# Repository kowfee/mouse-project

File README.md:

# mouse-diy
this project was inspired by https://github.com/wareya/DIY-Gaming-Mouse

!!!! ----- DO NOT CHANGE THE STRUCTURE OF THE FILES AND DIRECTORIES IN 'mouse-diy' ---- !!!!

!!!! ----- src/srom_3360_0x04.h should contain copyrighted material, so it is not included in this repository. 0x00 should be replaced with a correct sequence, available on the internet ---- !!!!
!!!! ----- it is firmware for the pmw3360 sensor. it will function without the firmware, however loses some of the functionality and precision ---- !!!!

[INSTALLATION]

- Windows: 
    - within the 'dist' folder run the "installer.exe"

- Linux: 
    - run the following commands from the 'mouse-diy' directory in the terminal:
        - chmod 744 bin/arduino-cli
        - chmod 744 dist/interface
        - bin/arduino-cli core install arduino:mbed_rp2040@4.1.5
        - sudo $HOME/.arduino15/packages/arduino/hardware/mbed_rp2040/4.1.5/post_install.sh
        - bin/arduino-cli config set library.enable_unsafe_install true
        - bin/arduino-cli lib install --zip-path files/Adafruit_NeoPixel-1.12.3.zip

[HOW TO USE]

- Windows:
    - run the 'interface.exe' within the 'dist' folder

- Linux:
    - from the 'mouse-diy' directory run the following command:
        - dist/interface

The user interface lets you choose how many DPI settings you want to save and the DPI for each setting. You can also adjust the RGB color for the static setting.

[UNINSTALL]

- Windows: 
    - run the following commands in CMD:
        - rmdir /s /q %USERPROFILE%\AppData\Local\Arduino15\packages\arduino\hardware\mbed_rp2040\
        - rmdir /s /q %USERPROFILE%\Documents\Arduino\libraries\Adafruit_NeoPixel\

- Linux:
    - run the following commands in the terminal:
        - rm -rf $HOME/.arduino15/packages/arduino/hardware/mbed_rp2040/
        - rm -rf $HOME/Arduino/libraries/Adafruit_Neopixel/

[LICENSE]
Adafruit NeoPixel is licensed under GNU Lesser General Public License https://github.com/adafruit/Adafruit_NeoPixel

Arduino CLI is licensed under GNU General Public License https://github.com/arduino/arduino-cli

relmouse_16.h is based on files from mbed OS, also licensed under the Apache License, version 2.0. https://github.com/arduino/ArduinoCore-mbed

The hardware design files ("PCB mit LED", "PCB_Fabrication_Files" "Fusion360-Base.f3z" and "Fusion360-Body.f3z") are licensed under the SolderpadLicense, version 2.1, as follows:
```
Copyright 2024 Pasty6969, klibandm, kowfee
SPDX-License-Identifier: Apache-2.0 WITH SHL-2.1

Licensed under the Solderpad Hardware License v 2.1 (the “License”); you may not use this file except in compliance with the License, or, at your option, the Apache License version 2.0. You may obtain a copy of the License at

https://solderpad.org/licenses/SHL-2.1/

Unless required by applicable law or agreed to in writing, any work distributed under the License is distributed on an “AS IS” BASIS, WITHOUT WARRANTIES OR CONDITIONS OF ANY KIND, either express or implied. See the License for the specific language governing permissions and limitations under the License.
```

mouse-diy.ino as well as other file contents are licensed under MIT License

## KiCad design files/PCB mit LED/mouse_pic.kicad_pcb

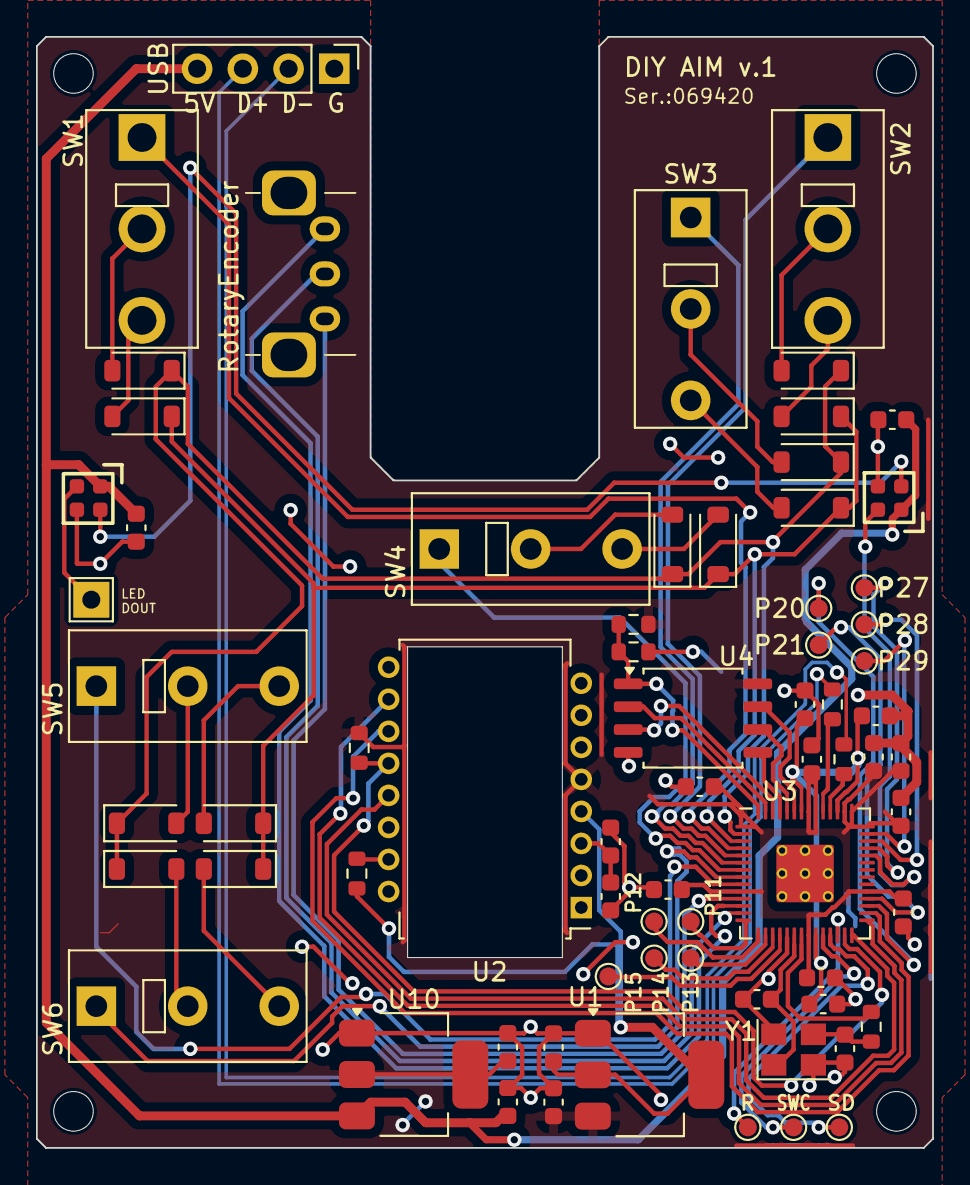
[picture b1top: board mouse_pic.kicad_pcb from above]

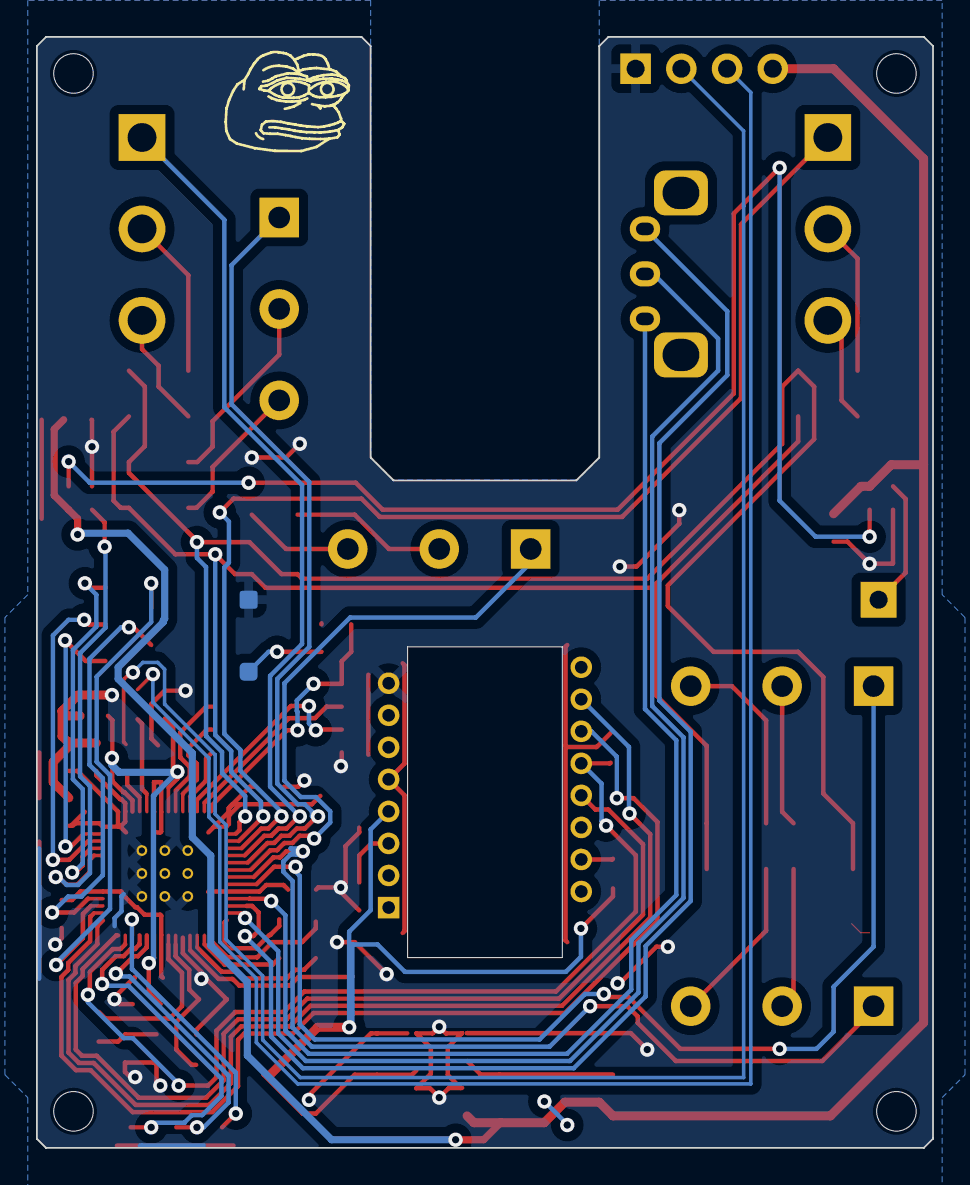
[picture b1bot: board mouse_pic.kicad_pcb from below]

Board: 2 copper layers, 49.8 x 61.7 mm, 72 parts (2 on the bottom side), 64 nets.

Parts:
C1, C2: 10uF; C_0603_1608Metric
C3: 100nF; C_0603_1608Metric
C4: 4.7uF; C_0603_1608Metric
C6, C7, C9, C11, C12, C13, C14, C15, C16, C17, C500: 100n; C_0603_1608Metric
C8, C10: 1u; C_0603_1608Metric
C100, C400: 10u; C_0603_1608Metric
C200, C300: 15p; C_0603_1608Metric
D1, D2, D3, D4, D5, D6, D7, D8, D9, D10, D11, D12: D; D_SOD-123
Encoder1: RotaryEncoder; Alps-EC10E1220501
LED1, LED2: LED_SK6812-EC20
LED_OUT1: DOUT; TestPoint_THTPad_2.0x2.0mm_Drill1.0mm
P11, P12, P13, P14, P15, P20, P21, P27, P28, P29, P30, P31, P32: TestPoint; TestPoint_Pad_D1.0mm
R1: 10K; R_0603_1608Metric
R3, R4: 27; R_0603_1608Metric
R40: R39; R_0603_1608Metric
R100, R500: 1k; R_0603_1608Metric
R200: 10k; R_0603_1608Metric
ResetGround: ResetGround
SW1, SW2, SW3, SW4, SW5, SW6: SW_SPDT; SW_Tactile_SPDT_Omron_D2F
U1: LM1117-1.8V; SOT-223-3_TabPin2
U2: PMW3360DM-T2QU; PixArt_PDIP-16_10.9x16.2mm_P1.78mm
U3: RP2040; RP2040-QFN-56
U4: W25Q32JVSS; SOIC-8_5.275x5.275mm_P1.27mm
U10: NCP1117-3.3_SOT223; SOT-223-3_TabPin2
USB1: USB; PinHeader_1x04_P2.54mm_Vertical
USB_BOOT1: Conn_01x01_Socket; TestPoint_THTPad_D2.0mm_Drill1.0mm_Edit
Y1: ABM8-272-T3; Crystal_SMD_3225-4Pin_3.2x2.5mm

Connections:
+1V1: C6.1, C7.1, C8.1, U3.23 (DVDD), U3.45 (VREG_VOUT), U3.50 (DVDD)
+3V3: C1.1, C9.1, C10.1, C11.1, C12.1, C13.1, C14.1, C15.1, C400.1, C500.1, R1.2, R200.1, U1.3 (VI), U2.5 (VDDIO), U3.1 (IOVDD), U3.10 (IOVDD), U3.22 (IOVDD), U3.33 (IOVDD), U3.42 (IOVDD), U3.43 (ADC_AVDD), U3.44 (VREG_IN), U3.48 (USB_VDD), U3.49 (IOVDD), U4.8 (VCC), U10.2 (VO)
/3360LED: R40.1, U2.15 (LED_P)
/ENC_A: Encoder1.A, U3.11 (GPIO8)
/ENC_B: Encoder1.B, U3.13 (GPIO10)
/ENC_C: Encoder1.C, U3.12 (GPIO9)
/GPIO0: D1.1 (K), D3.1 (K), D5.1 (K), D7.1 (K), D9.1 (K), D11.1 (K), U3.2 (GPIO0)
/GPIO1: D2.1 (K), D4.1 (K), D6.1 (K), D8.1 (K), D10.1 (K), D12.1 (K), U3.3 (GPIO1)
/GPIO2: SW1.2 (B), U3.4 (GPIO2)
/GPIO3: SW2.2 (B), U3.5 (GPIO3)
/GPIO4: SW3.2 (B), U3.6 (GPIO4)
/GPIO5: SW4.2 (B), U3.7 (GPIO5)
/GPIO6: SW6.2 (B), U3.8 (GPIO6)
/GPIO7: SW5.2 (B), U3.9 (GPIO7)
/GPIO11: P11.1, U3.14 (GPIO11)
/GPIO12: P12.1, U3.15 (GPIO12)
/GPIO13: P13.1, U3.16 (GPIO13)
/GPIO14: P14.1, U3.17 (GPIO14)
/GPIO15: P15.1, U3.18 (GPIO15)
/GPIO16: R1.1, U2.12 (MISO), U3.27 (GPIO16)
/GPIO17: U2.13 (NCS), U3.28 (GPIO17)
/GPIO18: U2.10 (SCLK), U3.29 (GPIO18)
/GPIO19: U2.11 (MOSI), U3.30 (GPIO19)
/GPIO20: P20.1, U3.31 (GPIO20)
/GPIO21: P21.1, U3.32 (GPIO21)
/GPIO26_ADC0: LED1.4 (DIN), U3.38 (GPIO26_ADC0)
/GPIO27_ADC1: P27.1, U3.39 (GPIO27_ADC1)
/GPIO28_ADC2: P28.1, U3.40 (GPIO28_ADC2)
/GPIO29_ADC3: P29.1, U3.41 (GPIO29_ADC3)
/QSPI_SCLK: U3.52 (QSPI_SCLK), U4.6 (CLK)
/QSPI_SD0: U3.53 (QSPI_SD0), U4.5 (DI(IO0))
/QSPI_SD1: U3.55 (QSPI_SD1), U4.2 (DO(IO1))
/QSPI_SD2: U3.54 (QSPI_SD2), U4.3 (IO2)
/QSPI_SD3: U3.51 (QSPI_SD3), U4.7 (IO3)
/QSPI_SS: R100.1, R200.2, U3.56 (QSPI_SS), U4.1 (~CS)
/RUN: P30.1, U3.26 (RUN)
/SWCLK: P31.1, U3.24 (SWCLK)
/SWD: P32.1, U3.25 (SWD)
/USBD+: R3.1, USB1.3
/USBD-: R4.1, USB1.2
/V2: C2.1, R40.2, U1.2 (VO), U2.4 (VDD)
/VDDPIX: C3.1, C4.1, U2.3 (VDDPIX)
/XIN: C200.1, U3.20 (XIN), Y1.1
/XOUT: R500.1, U3.21 (XOUT)
/~USB_BOOT: R100.2, USB_BOOT1.1
GND: C1.2, C2.2, C3.2, C4.2, C6.2, C7.2, C8.2, C9.2, C10.2, C11.2, C12.2, C13.2, C14.2, C15.2, C16.2, C17.2, C100.2, C200.2, C300.2, C400.2, C500.2, LED1.3 (GND), LED2.3 (GND), ResetGround.1, U1.1 (GND), U2.8 (GND), U3.19 (TESTEN), U3.57 (GND), U4.4 (GND), U10.1 (GND), USB1.1, Y1.2, Y1.4
unnamed: C300.1, R500.2, Y1.3
unnamed: D1.2 (A), SW1.1 (A)
unnamed: D2.2 (A), SW1.3 (C)
unnamed: D3.2 (A), SW2.1 (A)
unnamed: D4.2 (A), SW2.3 (C)
unnamed: D5.2 (A), SW3.1 (A)
unnamed: D6.2 (A), SW3.3 (C)
unnamed: D7.2 (A), SW4.1 (A)
unnamed: D8.2 (A), SW4.3 (C)
unnamed: D9.2 (A), SW5.1 (A)
unnamed: D10.2 (A), SW5.3 (C)
unnamed: D11.2 (A), SW6.1 (A)
unnamed: D12.2 (A), SW6.3 (C)
unnamed: LED1.2 (DOUT), LED2.4 (DIN)
unnamed: LED2.2 (DOUT), LED_OUT1.1
unnamed: R4.2, U3.46 (USB_DM)
unnamed: R3.2, U3.47 (USB_DP)
VBUS: C16.1, C17.1, C100.1, LED1.1 (VDD), LED2.1 (VDD), U10.3 (VI), USB1.4

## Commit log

2024-07-17 init
2024-07-18 Add files via upload
    Working code fo 0x04 firmware of pmw3360 with configurable DPI
2024-07-18 Update 3360_Mouse_pico.ino
    improved dpi button "if" statement to better register the button press
2024-07-22 add amount of dpi settings
2024-07-22 change entry widget to combobox, add faux-validation, add style to combobox
2024-07-22 add variable to define number of dpi values, remove debug code
2024-07-22 remove old debug code again
2024-07-23 Add files via upload
    added rgb:
    function rgb_select() calls the appropriate rgb mode
    function rainbow() switches colors in a rainbow pattern
    function static_color() sets led to a static color
    changed if statement for dpi_button in update_buttons() to act as an rgb switch as well as the dpi switch. must be held 2 seconds
2024-07-24 add colorwheel
2024-08-05 add colorwheel, rgb mode select, brightness scale
2024-08-08 change to form validity
2024-08-11 a somewhat functioning UI v1.0
2024-08-12 testing
2024-08-12 insert dpi .ino file
2024-08-12 add static rgb change in .ino file
2024-08-13 add switch case in .ino + add change mode select in .ino file
2024-09-23 Add files via upload
    Added "GLOBAL_BRIGHTNESS" variable to set global brightness for all modes. Line 185
    Assigning "NUM_DPI_VALUES" dynamically. Line 182
    Added "rgb_modes" and "NUM_RGB_MODES" to selectively enable them. Line 185-189
    Added "police()" (line 398), "rgb_off()" (line 356) and "breathing()" (line 432) functions.
    Colors for "breathing()" could be changed in uint32_t[] colors on line 418.
    Slightly changed call for "rgb_select()" in 468.
2024-09-26 add src folder
2024-10-28 fix mouse-project.ino path
2024-10-30 add installer script + ad way to upload on linux and windows
2024-10-30 update layout
2024-10-30 adjust layout
2024-10-31 fix bugs + add check if board is connected
2024-10-31 change file names
2024-10-31 add installer.exe and interface.exe for windows
2024-11-18 remove serial number check
2024-11-19 update readme with uninstall commands
2024-11-19 remove unused library
2024-11-19 Update README.md
    license
2024-11-19 Update srom_3360_0x04.h
    copyright scary
